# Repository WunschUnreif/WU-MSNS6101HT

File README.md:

# WU-MSNS6101HT

A module based on motion sensor MPU-6050 with a controllable heater to provide a constant working temperature.

The project uses KiCad for schematic and PCB drawing.

---
<br />This work is licensed under a <a rel="license" href="http://creativecommons.org/licenses/by/4.0/">Creative Commons Attribution 4.0 International License</a>.

---

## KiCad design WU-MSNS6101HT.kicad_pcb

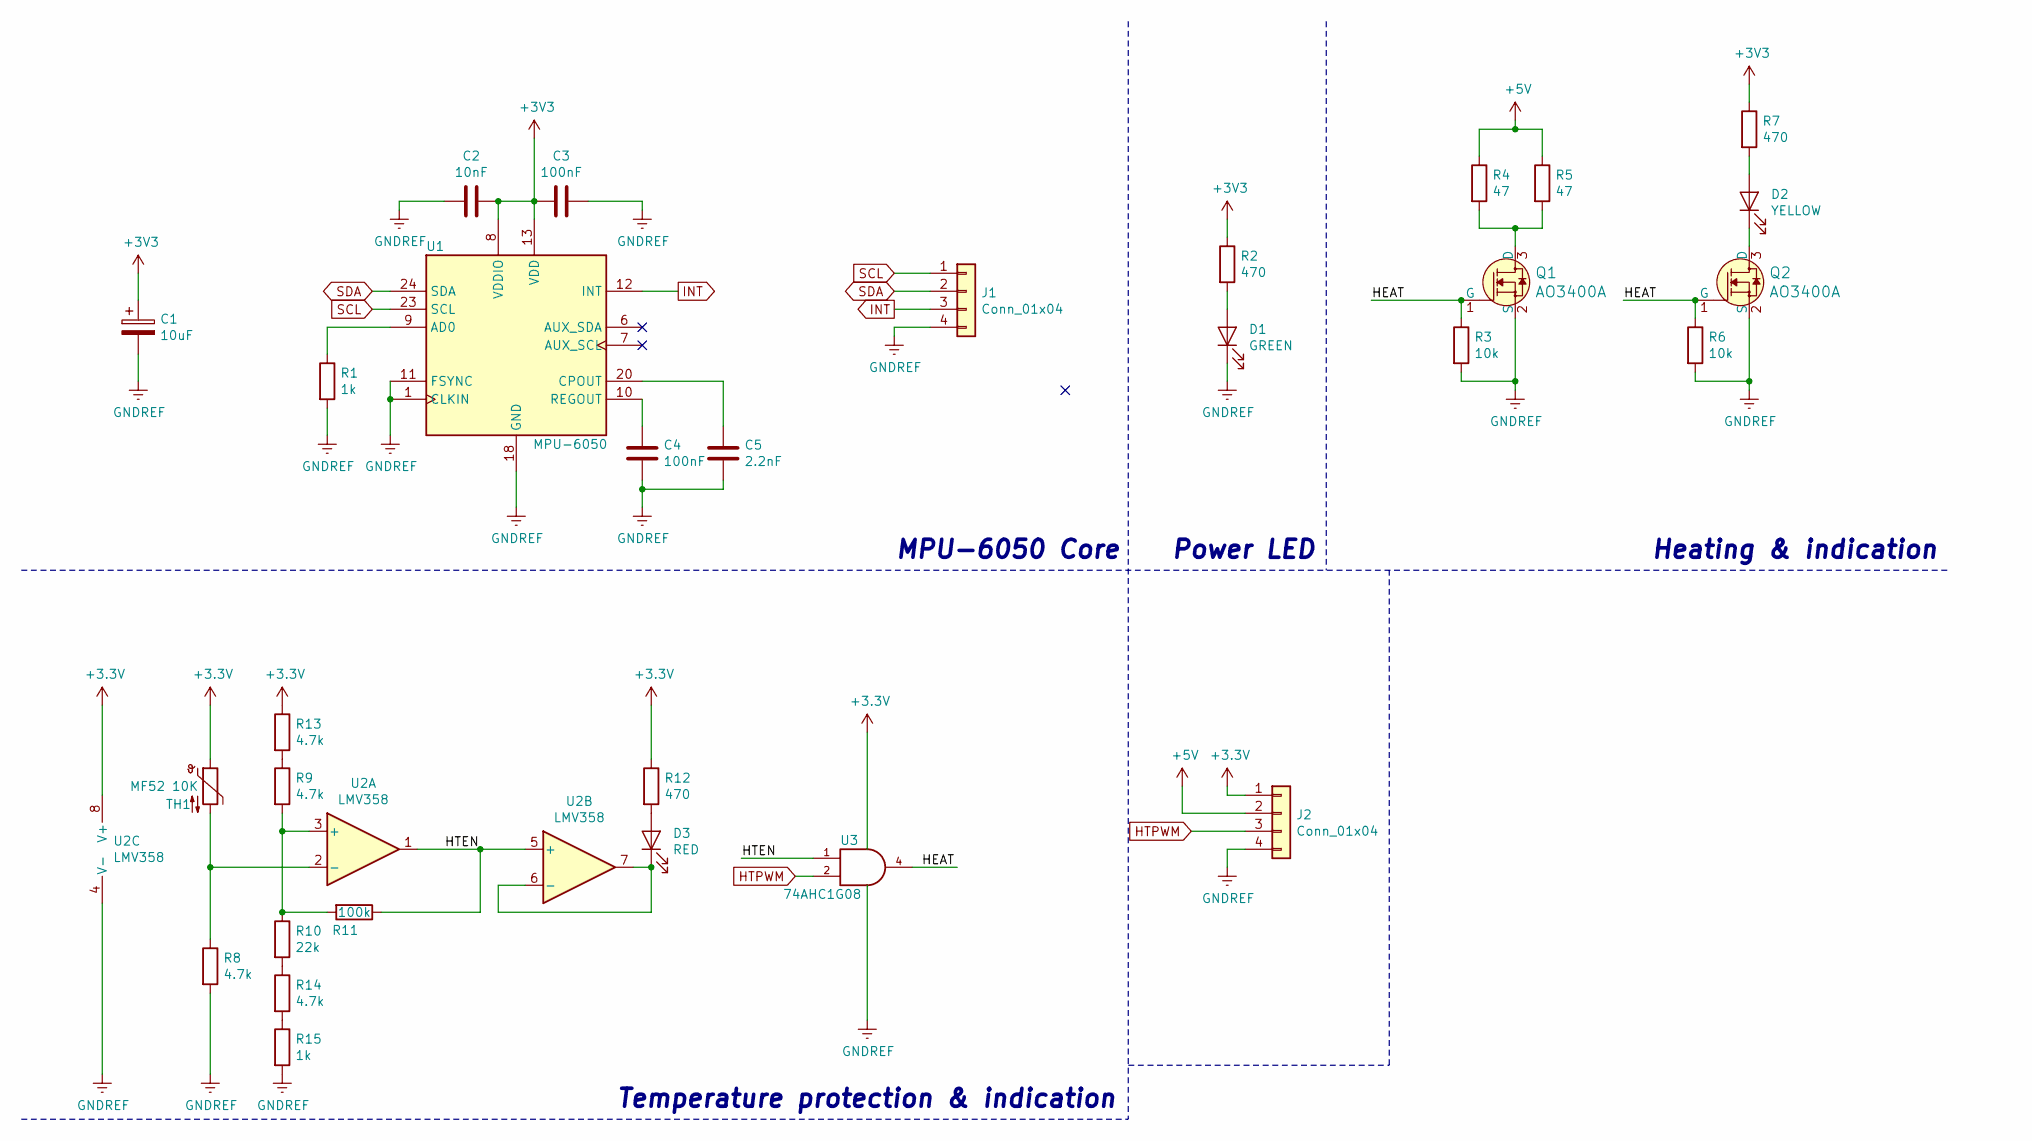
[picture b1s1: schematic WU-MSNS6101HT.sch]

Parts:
C1: 10uF; CP_EIA-3216-10_Kemet-I_Pad1.58x1.35mm_HandSolder
C2: 10nF; C_0805_2012Metric_Pad1.15x1.40mm_HandSolder
C3, C4: 100nF; C_0805_2012Metric_Pad1.15x1.40mm_HandSolder
C5: 2.2nF; C_0805_2012Metric_Pad1.15x1.40mm_HandSolder
D1: GREEN; LED_0805_2012Metric_Pad1.15x1.40mm_HandSolder
D2: YELLOW; LED_0805_2012Metric_Pad1.15x1.40mm_HandSolder
D3: RED; LED_0805_2012Metric_Pad1.15x1.40mm_HandSolder
J1, J2: Conn_01x04; PinSocket_1x04_P2.54mm_Vertical
Q1, Q2: AO3400A; SOT-23-3; MPN 2N7002; Digi-Key_PN 2N7002NCT-ND
R1, R15: 1k; R_0805_2012Metric_Pad1.15x1.40mm_HandSolder
R2, R7, R12: 470; R_0805_2012Metric_Pad1.15x1.40mm_HandSolder
R3, R6: 10k; R_0805_2012Metric_Pad1.15x1.40mm_HandSolder
R4, R5: 47; R_2512_6332Metric_Pad1.52x3.35mm_HandSolder
R8, R9, R13, R14: 4.7k; R_0805_2012Metric_Pad1.15x1.40mm_HandSolder
R10: 22k; R_0805_2012Metric_Pad1.15x1.40mm_HandSolder
R11: 100k; R_0805_2012Metric_Pad1.15x1.40mm_HandSolder
TH1: MF52 10K; PinHeader_1x02_P2.54mm_Vertical
U1: MPU-6050; InvenSense_QFN-24_4x4mm_P0.5mm
U2: LMV358; SOIC-8_3.9x4.9mm_P1.27mm
U3: 74AHC1G08; SOT-23-5_HandSoldering

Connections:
+5V: J2.2, R4.1, R5.1
/HEAT: Q1.1 (G), Q2.1 (G), R3.1, R6.1, U3.4
/HTEN: R11.1, U2.1, U2.5 (+), U3.1
GND: C1.2, C2.2, C3.1, C4.2, C5.2, D1.1 (K), J1.4, J2.4, Q1.2 (S), Q2.2 (S), R1.2, R3.2, R6.2, R8.2, R15.2, U1.1 (CLKIN), U1.11 (FSYNC), U1.18 (GND), U2.4 (V-), U3.3 (GND); also elsewhere on the board
HTPWM: J2.3, U3.2; also elsewhere on the board
INT: J1.3, U1.12 (INT)
unnamed: C4.1, U1.10 (REGOUT)
unnamed: C5.1, U1.20 (CPOUT)
unnamed: D1.2 (A), R2.2
unnamed: D2.1 (K), Q2.3 (D)
unnamed: D2.2 (A), R7.2
unnamed: D3.1 (K), U2.6 (-), U2.7
unnamed: D3.2 (A), R12.2
unnamed: Q1.3 (D), R4.2, R5.2
unnamed: R1.1, U1.9 (AD0)
unnamed: R8.1, TH1.2, U2.2 (-)
unnamed: R9.2, R10.1, R11.2, U2.3 (+)
unnamed: R10.2, R14.1
unnamed: R9.1, R13.2
unnamed: R14.2, R15.1
SCL: J1.1, U1.23 (SCL)
SDA: J1.2, U1.24 (SDA)

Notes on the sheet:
Heating & indication
Power LED
MPU-6050 Core
Temperature protection & indication

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
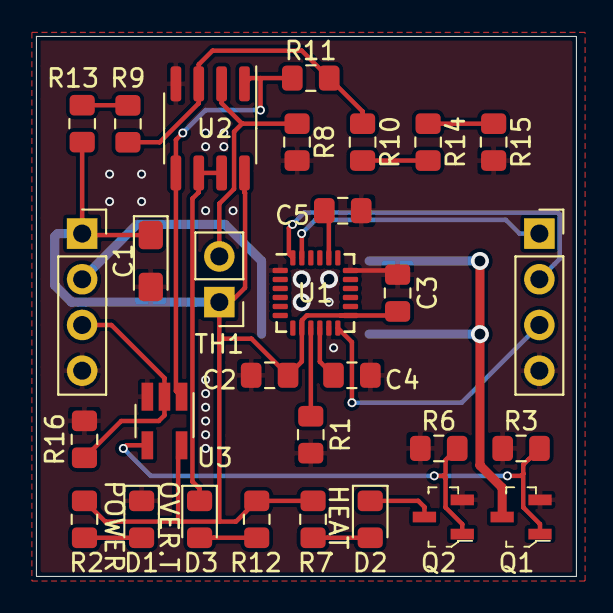
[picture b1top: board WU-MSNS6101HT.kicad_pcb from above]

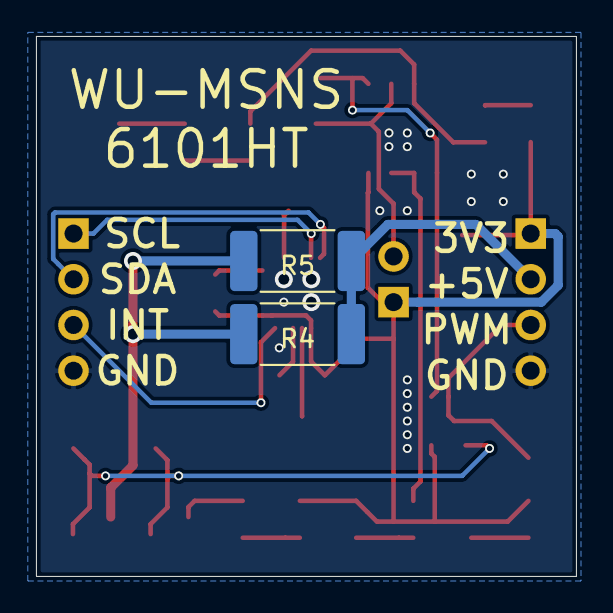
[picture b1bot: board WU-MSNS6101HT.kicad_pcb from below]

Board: 2 copper layers, 30.0 x 30.0 mm, 32 parts (2 on the bottom side), 23 nets.

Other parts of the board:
R16: 10k; R_0805_2012Metric_Pad1.15x1.40mm_HandSolder

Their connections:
GND: R16.2; also elsewhere on the board
HTPWM: R16.1; also elsewhere on the board

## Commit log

2019-08-24 Add a pull down res for
2019-08-24 Rework the PCB

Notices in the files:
WU-MSNS6101HT.kicad_pcb:
License: CC BY 4.0
WU-MSNS6101HT.sch:
https://creativecommons.org/licenses/by/4.0
Licence: CC BY 4.0
